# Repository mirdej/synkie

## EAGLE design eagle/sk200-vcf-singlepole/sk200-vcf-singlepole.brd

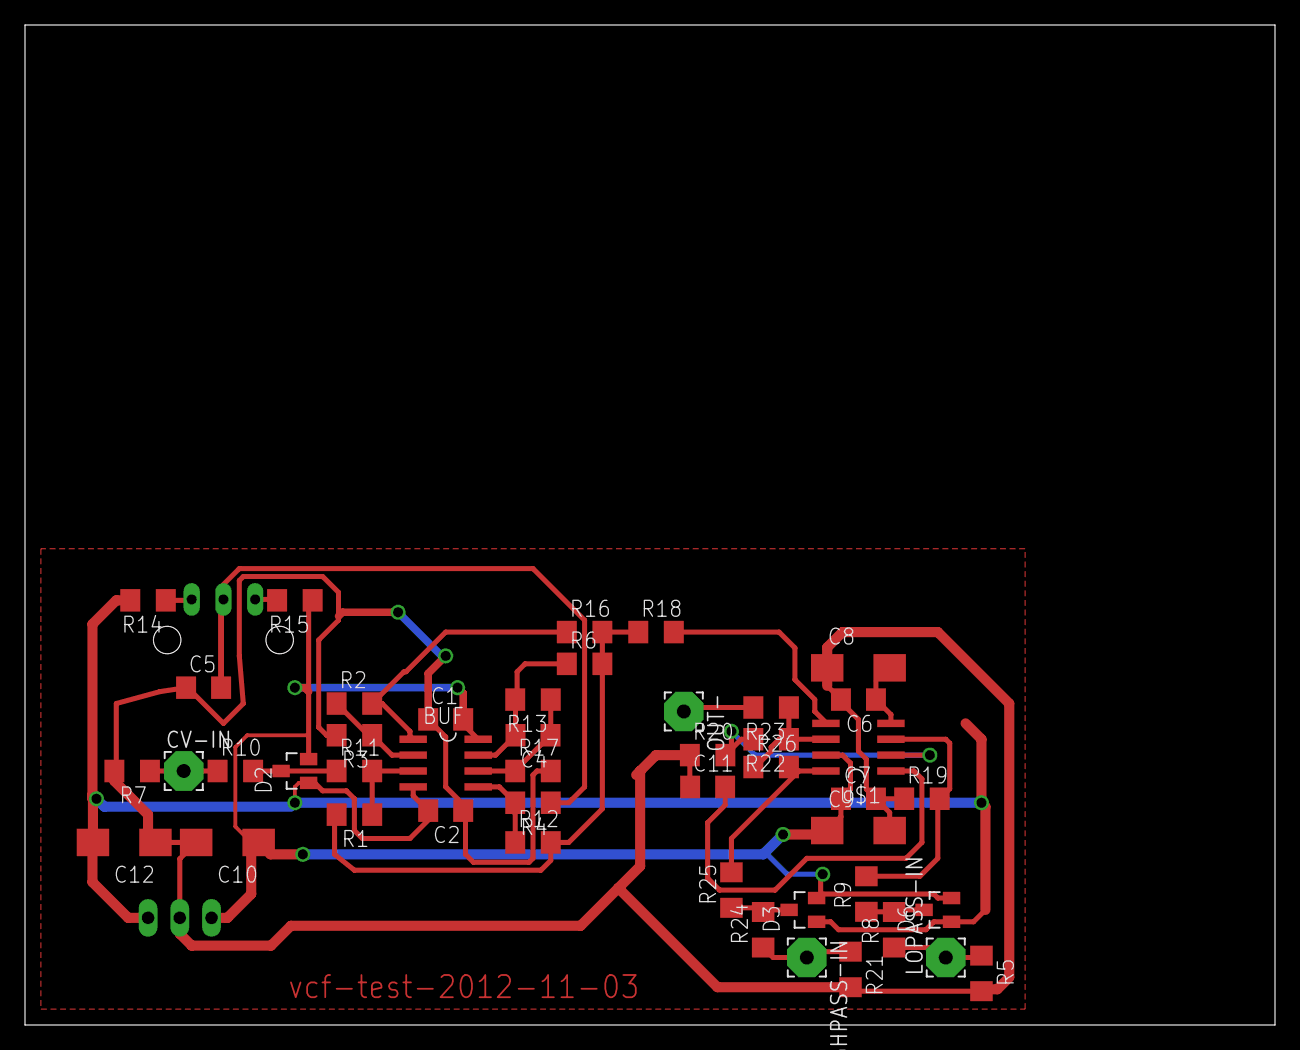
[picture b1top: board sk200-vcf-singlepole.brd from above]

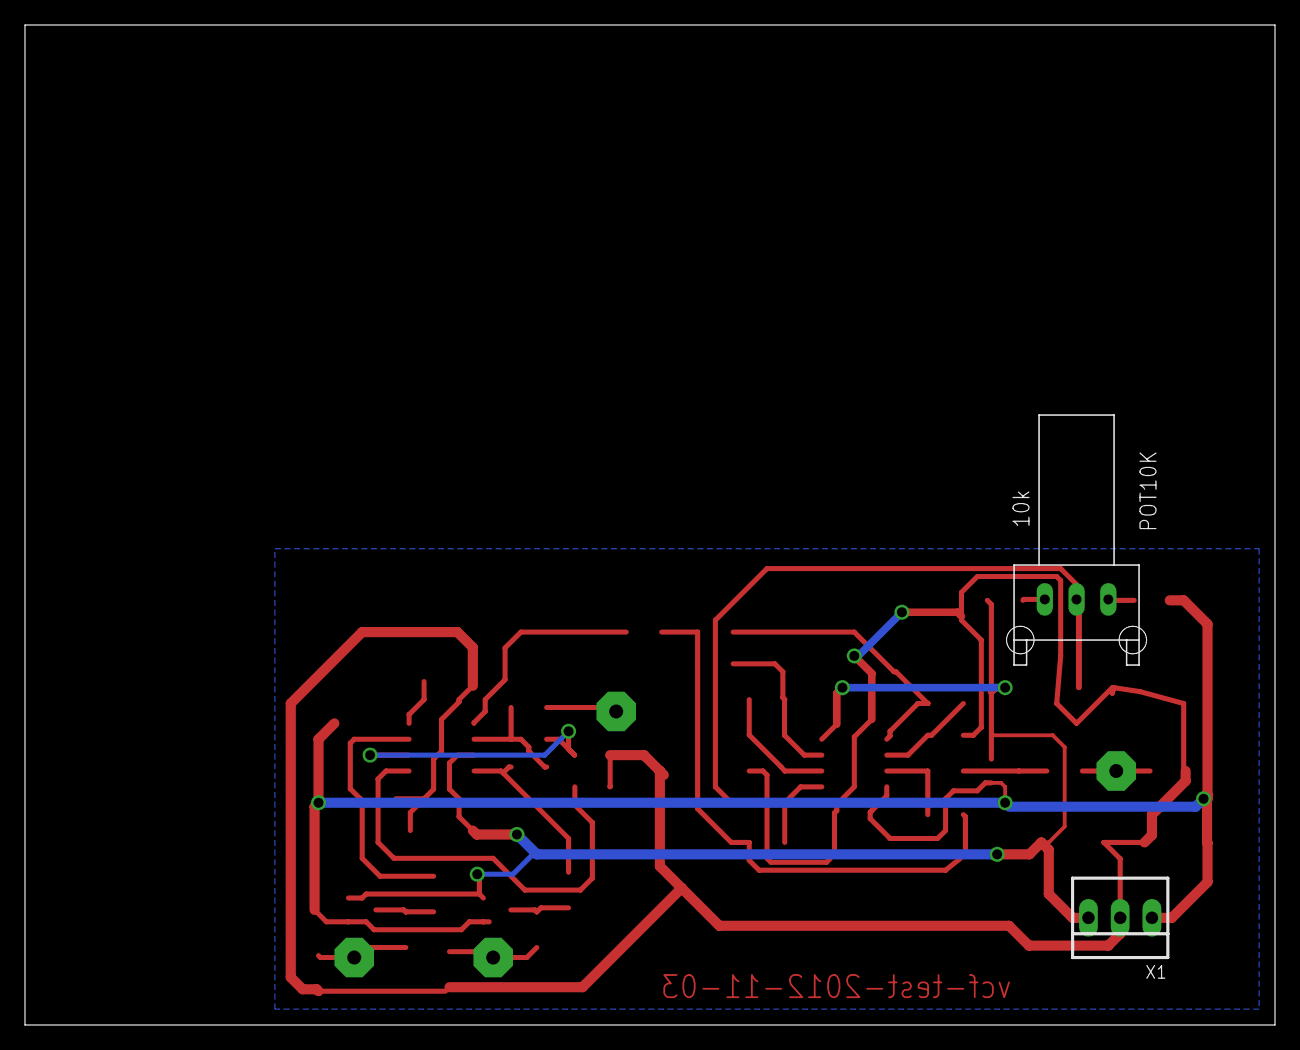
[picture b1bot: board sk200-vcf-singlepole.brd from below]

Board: 2 copper layers, 100.0 x 80.0 mm, 48 parts (2 on the bottom side), 26 nets.

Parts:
BUF: MAX4392ESA; SO08
C1, C2, C5, C6, C7: C1206
C4: 50p; C1206
C8, C9: 2u2tantal; CT6032
C10, C12: CT6032
C11: 330p (470p); C1206
CV-IN: 3,17/1,1
D2, D3, D6: BAT54S-L44; SOT23
HIGHPASS-IN: 3,17/1,1
LOPASS-IN: 3,17/1,1
OUT-: 3,17/1,1
POT10K: 10k; ALPS_RK09K111_H
R1, R2, R3, R11: 100k; R1206
R4, R12, R13, R17: 1M; R1206
R5, R21: 47k; R1206
R6, R9, R16, R22, R25, R26: 1k; R1206
R7: 4k7; R1206
R8, R10, R24: 100; R1206
R14, R15: 20k; R1206
R18: 1k6; R1206
R19, R20: 120; R1206
R23: 75; R1206
U$1: LT1228; SO08
X1: 22-23-2031

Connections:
+5V: BUF.8, C1.2, C7.1, C9.+, C10.+, D2.2, D3.2, D6.2, R15.1, U$1.7, X1.3
-5V: BUF.4, C2.2, C6.1, C8.-, C12.-, D2.1, D3.1, D6.1, R14.2, U$1.4, X1.1
GND: C1.1, C2.1, C5.1, C6.2, C7.2, C8.+, C9.-, C10.-, C11.1, C12.+, R3.2, R5.2, R7.2, R17.2, R19.1, R20.1, R21.2, X1.2
unnamed: C5.2, POT10K.2, R4.1
unnamed: POT10K.1, R14.1
unnamed: POT10K.3, R15.2
unnamed: BUF.2, R2.1, R3.1
unnamed: R9.2, R19.2, U$1.3
unnamed: C11.2, U$1.1
unnamed: BUF.5, R4.2, R12.1
unnamed: BUF.7, C4.2, R6.1, R13.2
unnamed: R20.2, R22.2, U$1.2
unnamed: CV-IN.1, R7.1, R10.1
unnamed: D2.3, R10.2, R11.1
unnamed: BUF.6, C4.1, R13.1, R17.1
unnamed: BUF.3, R1.1, R11.2
unnamed: LOPASS-IN.1, R5.1, R8.1
unnamed: D6.3, R8.2, R9.1
unnamed: BUF.1, R2.2, R16.1
unnamed: R18.2, U$1.5
unnamed: R1.2, R6.2, R12.2, R16.2, R18.1
unnamed: R22.1, R23.1, R26.1, U$1.6
unnamed: OUT-.1, R23.2
unnamed: HIGHPASS-IN.1, R21.1, R24.1
unnamed: D3.3, R24.2, R25.1
unnamed: R25.2, R26.2, U$1.8

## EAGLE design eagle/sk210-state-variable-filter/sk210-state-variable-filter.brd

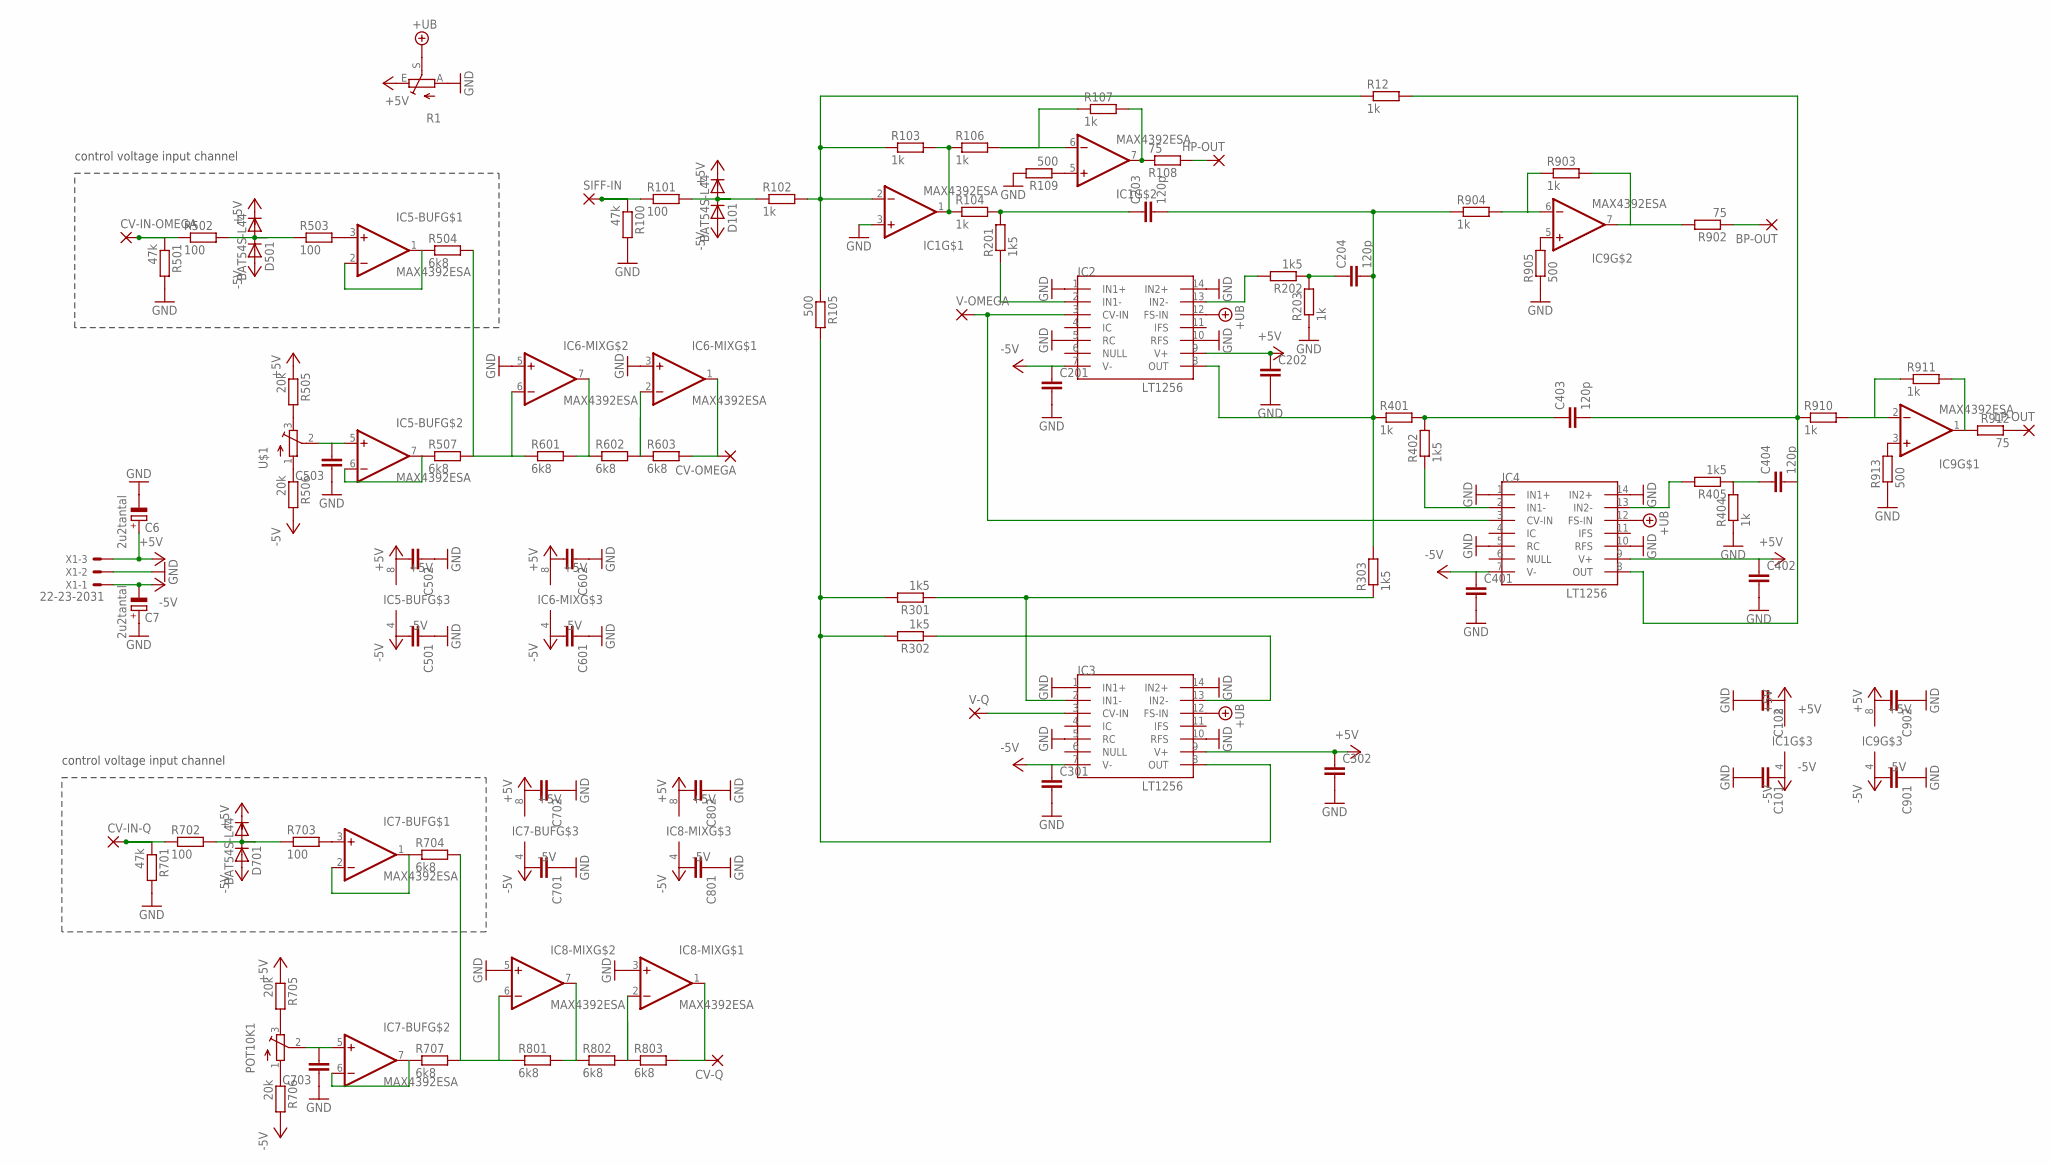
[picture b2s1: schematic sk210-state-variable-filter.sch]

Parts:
BP-OUT: 3,17/1,1
C6, C7: 2u2tantal; CT3528
C101, C102, C201, C202, C301, C302, C401, C402, C501, C502, C503, C601, C602, C701, C702, C703, C801, C802, C901, C902: C-EUC1206; C1206
C203, C204, C403, C404: 120p; C1206
CV-IN-OMEGA: 3,17/1,1
CV-IN-Q: 3,17/1,1
CV-OMEGA: 3,17/1,1
CV-Q: 3,17/1,1
D101, D501, D701: BAT54S-L44; SOT23
HP-OUT: 3,17/1,1
IC1, IC5-BUF, IC6-MIX, IC7-BUF, IC8-MIX, IC9: MAX4392ESA; SO08
IC2, IC3, IC4: LT1256; SO14
LP-OUT: 3,17/1,1
POT10K1: 10k; ALPS_RK09K111
R1: TRIM_EU-B64W; B64W
R12, R102, R103, R104, R106, R107, R203, R401, R404, R903, R904, R910, R911: 1k; R1206
R100, R501, R701: 47k; R1206
R101, R502, R503, R702, R703: 100; R1206
R105, R109, R905, R913: 500; R1206
R108, R902, R912: 75; R1206
R201, R202, R301, R302, R303, R402, R405: 1k5; R1206
R504, R507, R601, R602, R603, R704, R707, R801, R802, R803: 6k8; R1206
R505, R506, R705, R706: 20k; R1206
SIFF-IN: 3,17/1,1
U$1: ALPS_RK09K111_HOHNE-FüSSE; ALPS_RK09K111
V-OMEGA: 3,17/1,1
V-Q: 3,17/1,1
X1: 22-23-2031

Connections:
+5V: C6.+, C102.1, C202.1, C302.1, C402.1, C502.2, C602.2, C702.2, C802.2, C902.2, D101.2 (C), D501.2 (C), D701.2 (C), IC1.8 (+5V), IC2.9 (V+), IC3.9 (V+), IC4.9 (V+), IC5-BUF.8 (+5V), IC6-MIX.8 (+5V), IC7-BUF.8 (+5V), IC8-MIX.8 (+5V), IC9.8 (+5V), R1.E, R505.1, R705.1, X1.3
+UB: IC2.12 (FS-IN), IC3.12 (FS-IN), IC4.12 (FS-IN), R1.S
-5V: C7.-, C101.1, C201.1, C301.1, C401.1, C501.2, C601.2, C701.2, C801.2, C901.2, D101.1 (A), D501.1 (A), D701.1 (A), IC1.4 (-5V), IC2.7 (V-), IC3.7 (V-), IC4.7 (V-), IC5-BUF.4 (-5V), IC6-MIX.4 (-5V), IC7-BUF.4 (-5V), IC8-MIX.4 (-5V), IC9.4 (-5V), R506.2, R706.2, X1.1
GND: C6.-, C7.+, C101.2, C102.2, C201.2, C202.2, C301.2, C302.2, C401.2, C402.2, C501.1, C502.1, C503.1, C601.1, C602.1, C701.1, C702.1, C703.1, C801.1, C802.1, C901.1, C902.1, IC1.3 (+IN), IC2.1 (IN1+), IC2.5 (RC), IC2.10 (RFS), IC2.14 (IN2+), IC3.1 (IN1+), IC3.5 (RC), IC3.10 (RFS), IC3.14 (IN2+), IC4.1 (IN1+), IC4.5 (RC), IC4.10 (RFS), IC4.14 (IN2+), IC6-MIX.3 (+IN), IC6-MIX.5 (+IN), IC8-MIX.3 (+IN), IC8-MIX.5 (+IN), R1.A, R100.2, R109.2, R203.1, R404.1, R501.2, R701.2, R905.1, R913.1, X1.2
unnamed: C503.2, IC5-BUF.5 (+IN), U$1.2 (W)
unnamed: R506.1, U$1.1 (S)
unnamed: R505.2, U$1.3 (E)
unnamed: IC1.7 (OUT), R107.2, R108.1
unnamed: IC1.2 (-IN), R12.1, R102.2, R103.1, R105.1
unnamed: C203.1, R104.2, R201.2
unnamed: C203.2, C204.2, IC2.8 (OUT), R303.2, R401.1, R904.1
unnamed: IC3.2 (IN1-), R301.1, R303.1
unnamed: IC3.8 (OUT), R105.2, R301.2, R302.2
unnamed: CV-IN-OMEGA.1, R501.1, R502.1
unnamed: D501.3 (AC), R502.2, R503.1
unnamed: IC2.2 (IN1-), R201.1
unnamed: IC5-BUF.6 (-IN), IC5-BUF.7 (OUT), R507.1
unnamed: IC5-BUF.3 (+IN), R503.2
unnamed: R100.1, R101.1, SIFF-IN.1
unnamed: D101.3 (AC), R101.2, R102.1
unnamed: IC5-BUF.1 (OUT), IC5-BUF.2 (-IN), R504.1
unnamed: IC3.13 (IN2-), R302.1
unnamed: IC6-MIX.6 (-IN), R504.2, R507.2, R601.1
unnamed: IC6-MIX.7 (OUT), R601.2, R602.1
unnamed: IC6-MIX.2 (-IN), R602.2, R603.1
unnamed: CV-OMEGA.1, IC6-MIX.1 (OUT), R603.2
unnamed: IC3.3 (CV-IN), V-Q.1
unnamed: IC2.3 (CV-IN), IC4.3 (CV-IN), V-OMEGA.1
unnamed: CV-IN-Q.1, R701.1, R702.1
unnamed: IC2.13 (IN2-), R202.2
unnamed: C204.1, R202.1, R203.2
unnamed: C403.1, R401.2, R402.2
unnamed: C403.2, C404.2, IC4.8 (OUT), R12.2, R910.1
unnamed: IC4.2 (IN1-), R402.1
unnamed: D701.3 (AC), R702.2, R703.1
unnamed: C404.1, R404.2, R405.1
unnamed: IC7-BUF.3 (+IN), R703.2
unnamed: IC7-BUF.1 (OUT), IC7-BUF.2 (-IN), R704.1
unnamed: IC7-BUF.6 (-IN), IC7-BUF.7 (OUT), R707.1
unnamed: IC8-MIX.6 (-IN), R704.2, R707.2, R801.1
unnamed: IC8-MIX.7 (OUT), R801.2, R802.1
unnamed: IC8-MIX.2 (-IN), R802.2, R803.1
unnamed: CV-Q.1, IC8-MIX.1 (OUT), R803.2
unnamed: C703.2, IC7-BUF.5 (+IN), POT10K1.2 (W)
unnamed: POT10K1.1 (S), R706.1
unnamed: POT10K1.3 (E), R705.2
unnamed: IC9.1 (OUT), R911.2, R912.2
unnamed: HP-OUT.1, R108.2
unnamed: IC9.7 (OUT), R902.2, R903.2
unnamed: IC1.1 (OUT), R103.2, R104.1, R106.1
unnamed: LP-OUT.1, R912.1
unnamed: BP-OUT.1, R902.1
unnamed: IC9.6 (-IN), R903.1, R904.2
unnamed: IC9.5 (+IN), R905.2
unnamed: IC1.6 (-IN), R106.2, R107.1
unnamed: IC1.5 (+IN), R109.1
unnamed: IC9.2 (-IN), R910.2, R911.1
unnamed: IC9.3 (+IN), R913.2
R403: IC4.13 (IN2-), R405.2

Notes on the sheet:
control voltage input channel

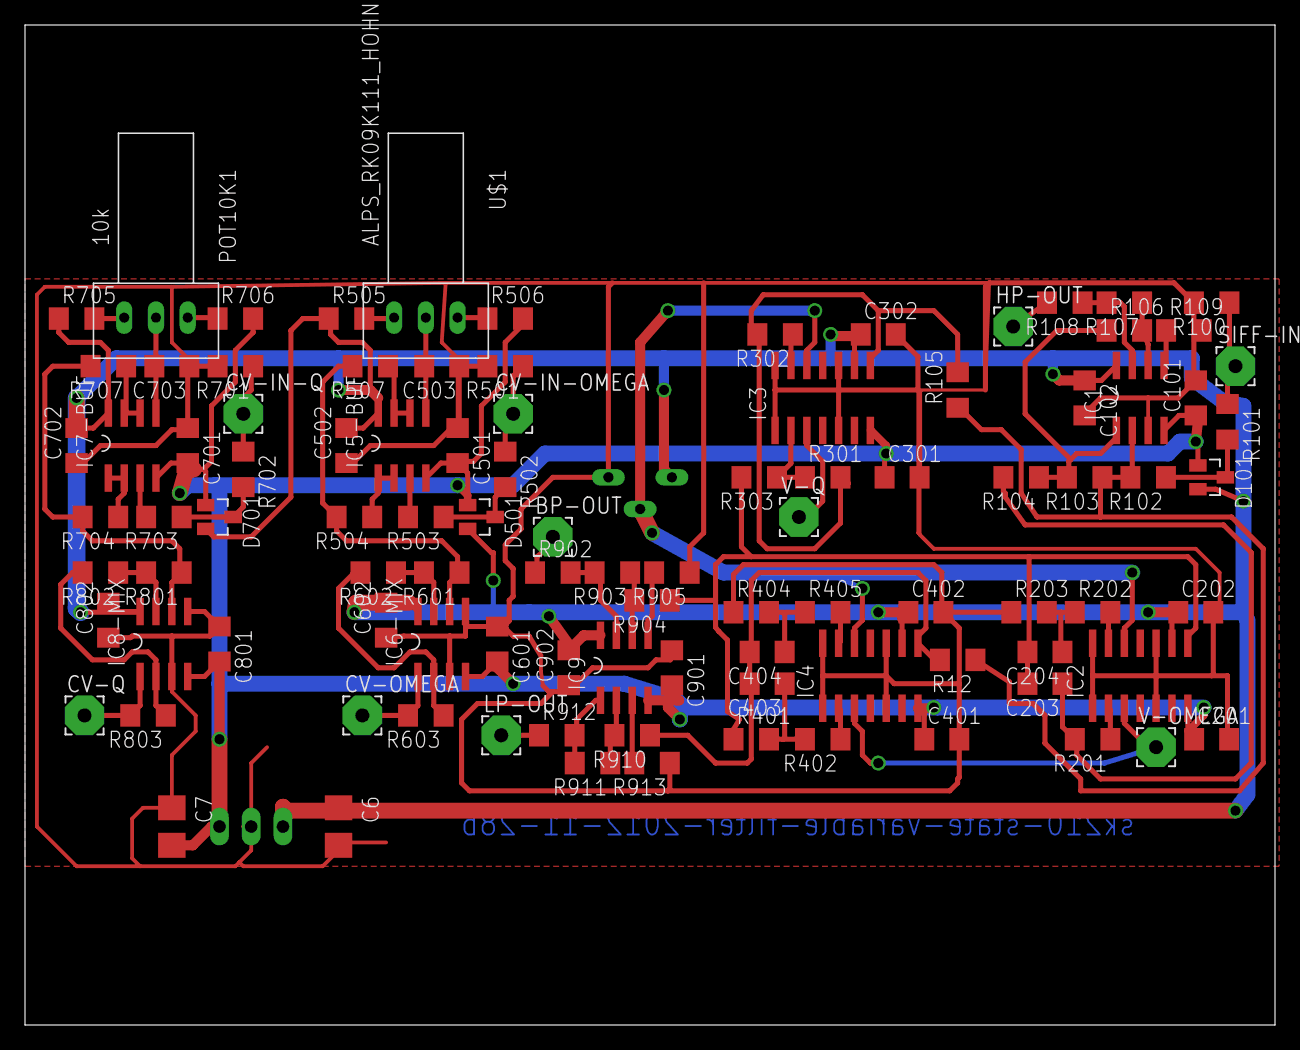
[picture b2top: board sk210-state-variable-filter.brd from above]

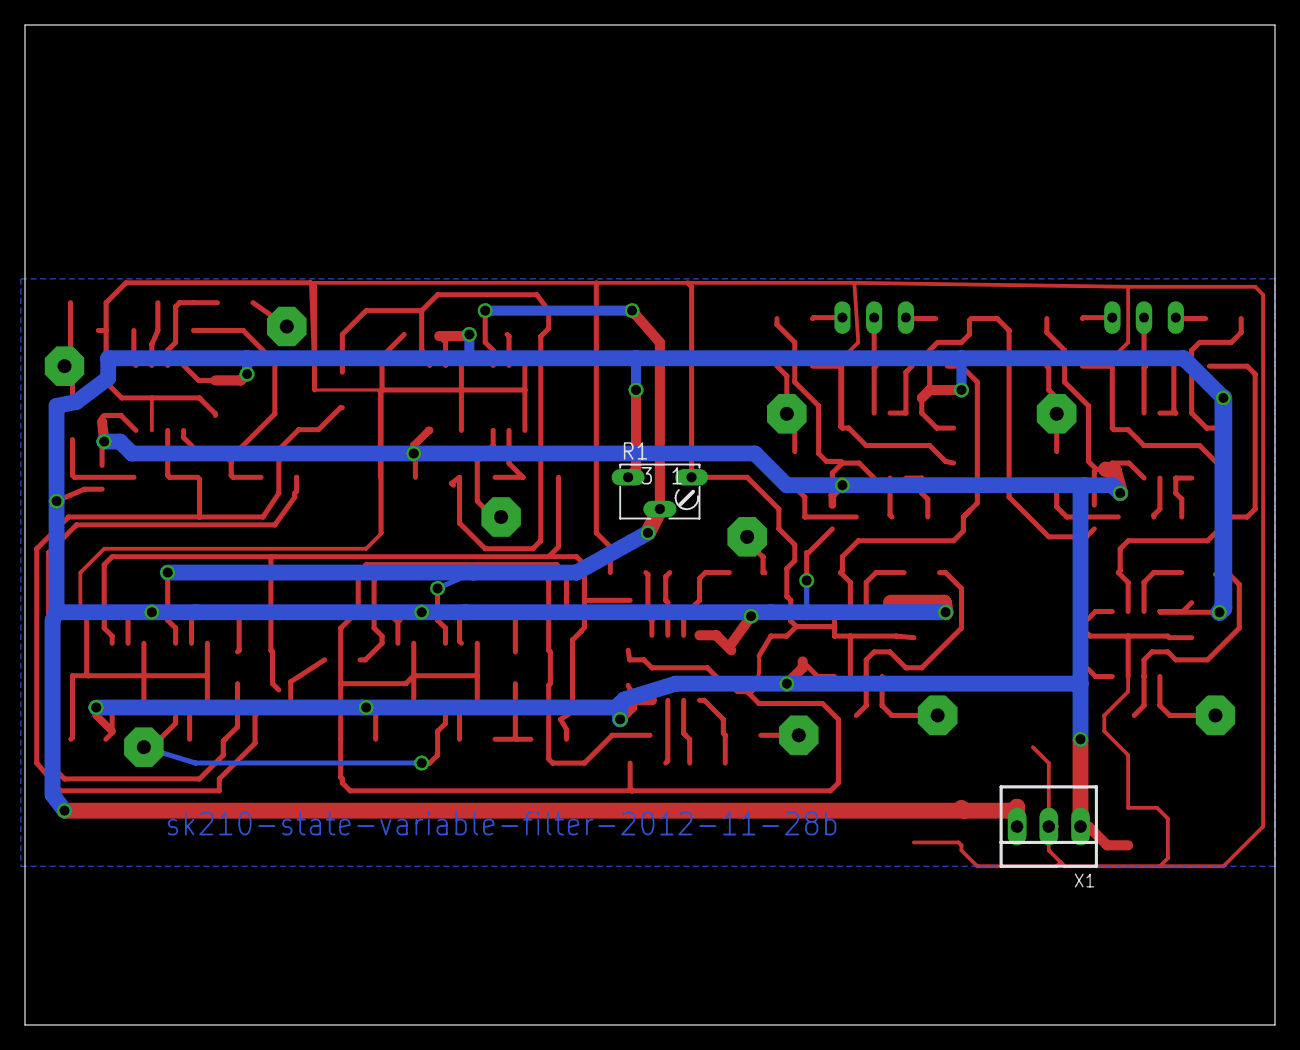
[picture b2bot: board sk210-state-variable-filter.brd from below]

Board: 2 copper layers, 100.0 x 80.0 mm, 101 parts (2 on the bottom side), 59 nets.

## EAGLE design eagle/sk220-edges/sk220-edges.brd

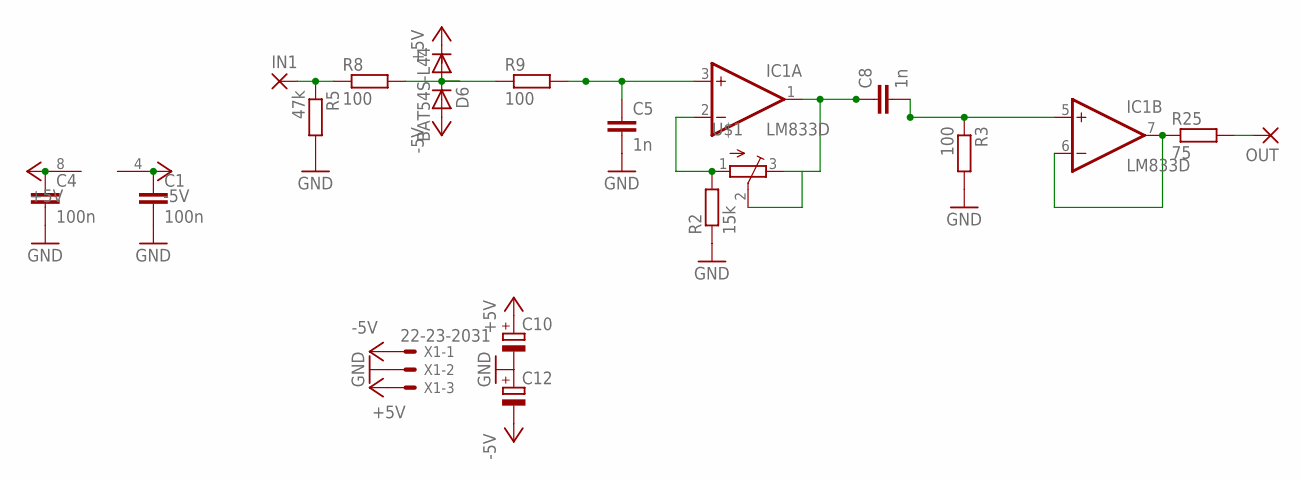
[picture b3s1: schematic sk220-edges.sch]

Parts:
C1, C4: 100n; C0603
C5, C8: 1n; C1206
C10, C12: CPOL-EUSMCB; SMC_B
D6: BAT54S-L44; SOT23
IC1: LM833D; SO08
IN1: 3,81/1,1
OUT: 3,81/1,1
R2: 15k; R1206
R3, R8, R9: 100; R1206
R5: 47k; R1206
R25: 75; R1206
U$1: ALPS_RK09K111_HOHNE-FüSSE; ALPS_RK09K111
X1: 22-23-2031

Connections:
+5V: C4.1, C10.+, D6.2 (C), IC1.8 (V+), X1.3
-5V: C1.1, C12.-, D6.1 (A), IC1.4 (V-), X1.1
GND: C1.2, C4.2, C5.2, C10.-, C12.+, R2.1, R3.2, R5.2, X1.2
unnamed: IC1.2 (-IN), R2.2, U$1.1 (S)
unnamed: OUT.1, R25.2
unnamed: C8.2, IC1.5 (+IN), R3.1
unnamed: C5.1, IC1.3 (+IN), R9.2
unnamed: IC1.6 (-IN), IC1.7 (OUT), R25.1
unnamed: C8.1, IC1.1 (OUT), U$1.2 (W), U$1.3 (E)
unnamed: IN1.1, R5.1, R8.1
unnamed: D6.3 (AC), R8.2, R9.1

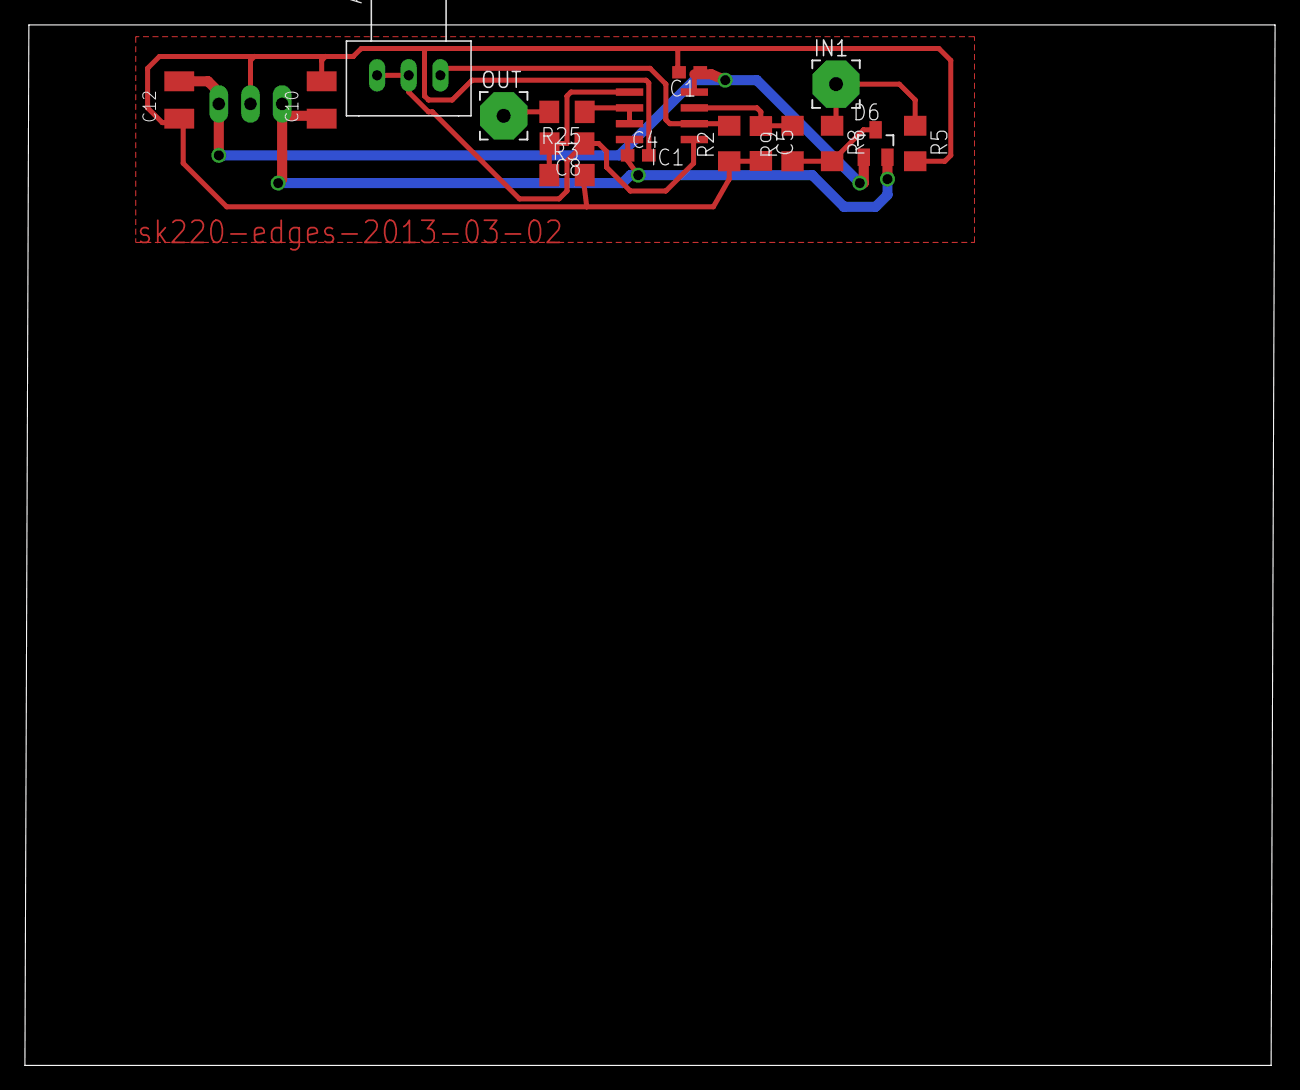
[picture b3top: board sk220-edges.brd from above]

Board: 2 copper layers, 100.3 x 83.5 mm, 18 parts (1 on the bottom side), 11 nets.

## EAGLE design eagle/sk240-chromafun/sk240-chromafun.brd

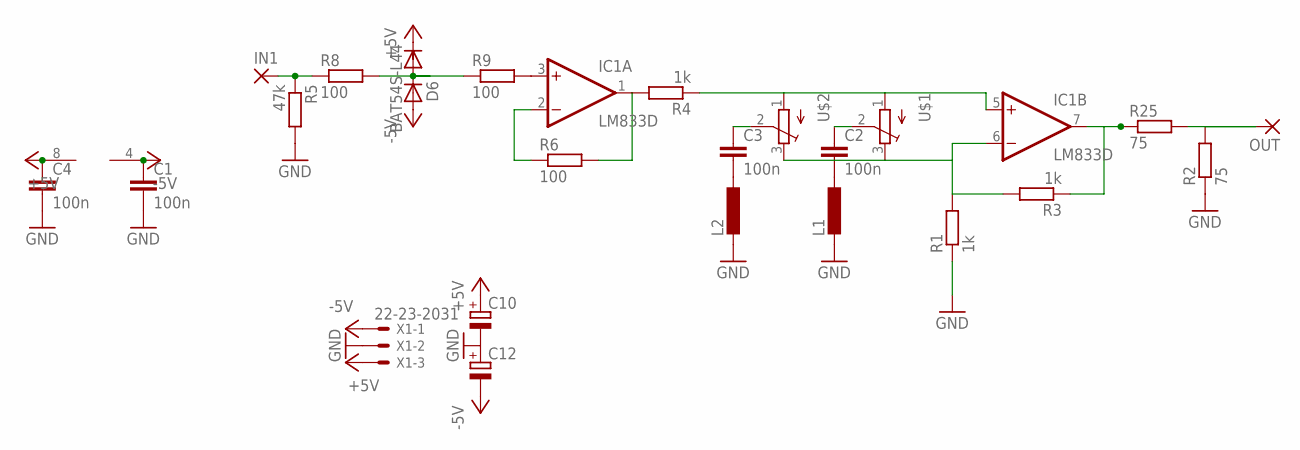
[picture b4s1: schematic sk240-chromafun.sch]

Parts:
C1, C2, C3, C4: 100n; C0603
C10, C12: CPOL-EUSMCB; SMC_B
D6: BAT54S-L44; SOT23
IC1: LM833D; SO08
IN1: 3,81/1,1
L1, L2: L-EU0207/12; 0207/12
OUT: 3,81/1,1
R1, R3, R4: 1k; R1206
R2, R25: 75; R1206
R5: 47k; R1206
R6, R8, R9: 100; R1206
U$1, U$2: ALPS_RK09K111_HOHNE-FüSSE; ALPS_RK09K111
X1: 22-23-2031

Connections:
+5V: C4.1, C10.+, D6.2 (C), IC1.8 (V+), X1.3
-5V: C1.1, C12.-, D6.1 (A), IC1.4 (V-), X1.1
GND: C1.2, C4.2, C10.-, C12.+, L1.2, L2.2, R1.1, R2.1, R5.2, X1.2
unnamed: IC1.1 (OUT), R4.2, R6.2
unnamed: OUT.1, R2.2, R25.2
unnamed: IC1.3 (+IN), R9.2
unnamed: IC1.7 (OUT), R3.1, R25.1
unnamed: IC1.6 (-IN), R1.2, R3.2, U$1.3 (E), U$2.3 (E)
unnamed: IC1.5 (+IN), R4.1, U$1.1 (S), U$2.1 (S)
unnamed: C2.1, U$1.2 (W)
unnamed: C2.2, L1.1
unnamed: C3.1, U$2.2 (W)
unnamed: C3.2, L2.1
unnamed: IC1.2 (-IN), R6.1
unnamed: IN1.1, R5.1, R8.1
unnamed: D6.3 (AC), R8.2, R9.1

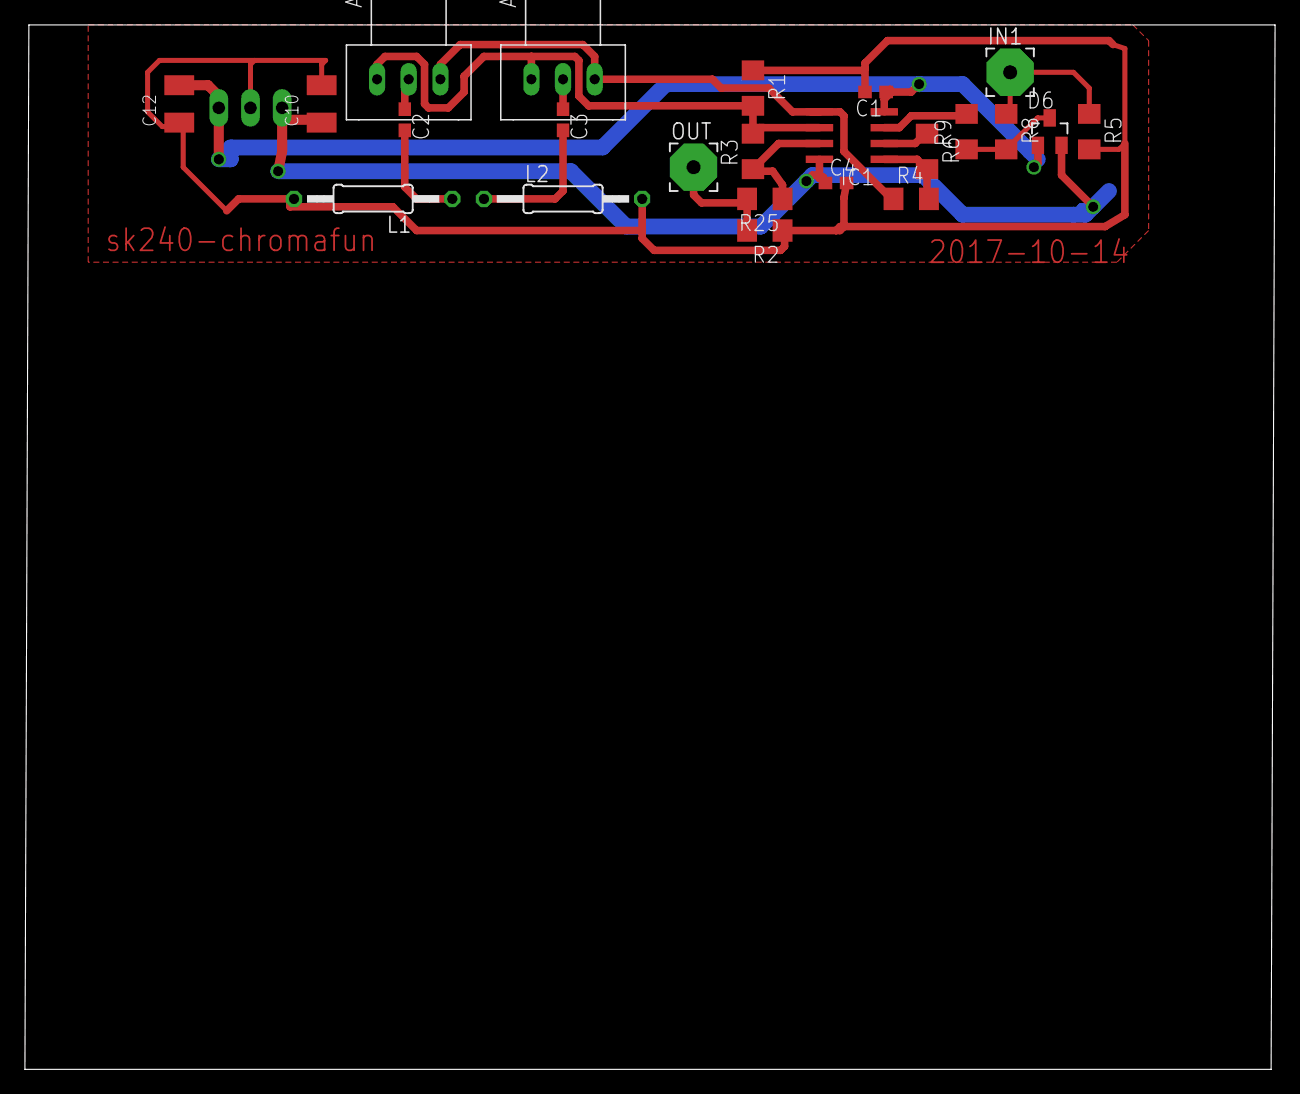
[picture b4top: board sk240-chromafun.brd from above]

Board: 2 copper layers, 100.3 x 83.8 mm, 24 parts (1 on the bottom side), 16 nets.

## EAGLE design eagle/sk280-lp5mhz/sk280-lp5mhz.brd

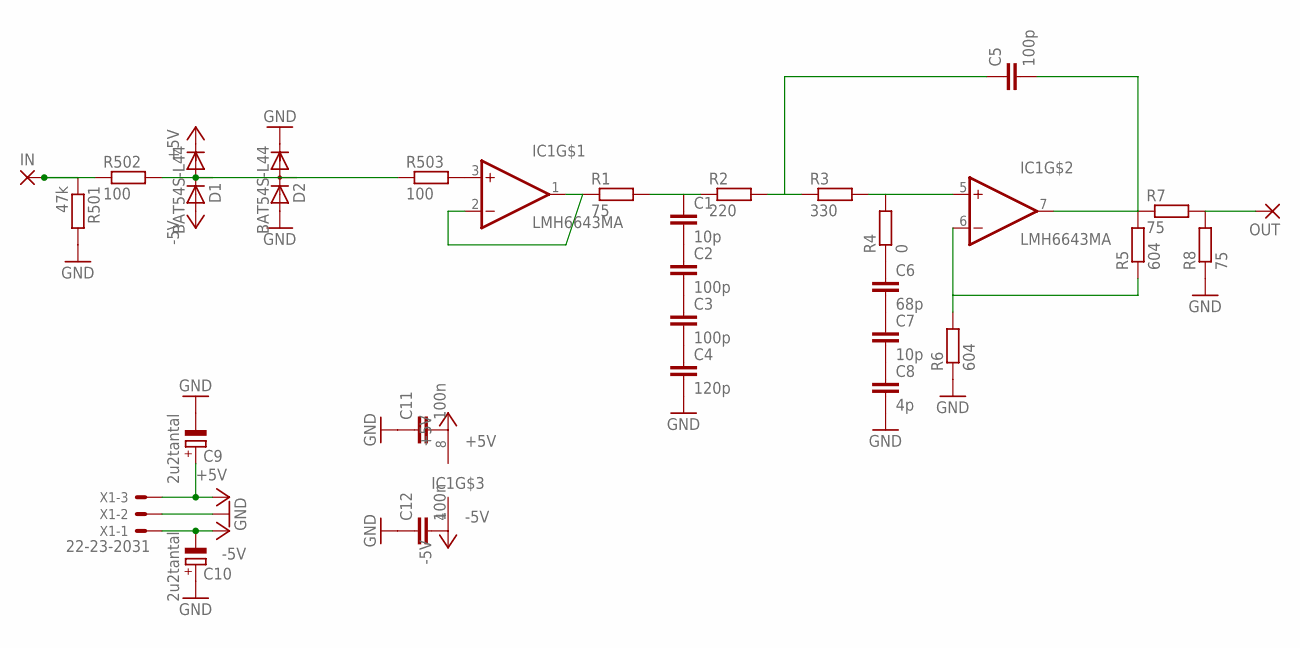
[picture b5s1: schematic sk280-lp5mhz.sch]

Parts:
C1, C7: 10p; C1206
C2, C3, C5: 100p; C1206
C4: 120p; C1206
C6: 68p; C1206
C8: 4p; C1206
C9, C10: 2u2tantal; CT3528
C11, C12: 100n; C0603
D1, D2: BAT54S-L44; SOT23
IC1: LMH6643MA; SO08
IN: 3,17/1,1
OUT: 3,17/1,1
R1, R7, R8: 75; R1206
R2: 220; R1206
R3: 330; R1206
R4: 0; R1206
R5, R6: 604; R1206
R501: 47k; R1206
R502, R503: 100; R1206
X1: 22-23-2031

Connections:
+5V: C9.+, C11.2, D1.2 (C), IC1.8 (+5V), X1.3
-5V: C10.-, C12.2, D1.1 (A), IC1.4 (-5V), X1.1
GND: C4.2, C8.2, C9.-, C10.+, C11.1, C12.1, D2.1 (A), D2.2 (C), R6.1, R8.1, R501.2, X1.2
unnamed: IC1.3 (+IN), R503.2
unnamed: IC1.1 (OUT), IC1.2 (-IN), R1.1
unnamed: C1.2, C2.1
unnamed: C2.2, C3.1
unnamed: C3.2, C4.1
unnamed: C1.1, R1.2, R2.1
unnamed: C5.1, R2.2, R3.1
unnamed: IC1.5 (+IN), R3.2, R4.2
unnamed: C5.2, IC1.7 (OUT), R5.2, R7.1
unnamed: IN.1, R501.1, R502.1
unnamed: D1.3 (AC), D2.3 (AC), R502.2, R503.1
unnamed: C6.1, R4.1
unnamed: C6.2, C7.1
unnamed: C7.2, C8.1
unnamed: IC1.6 (-IN), R5.1, R6.2
unnamed: OUT.1, R7.2, R8.2

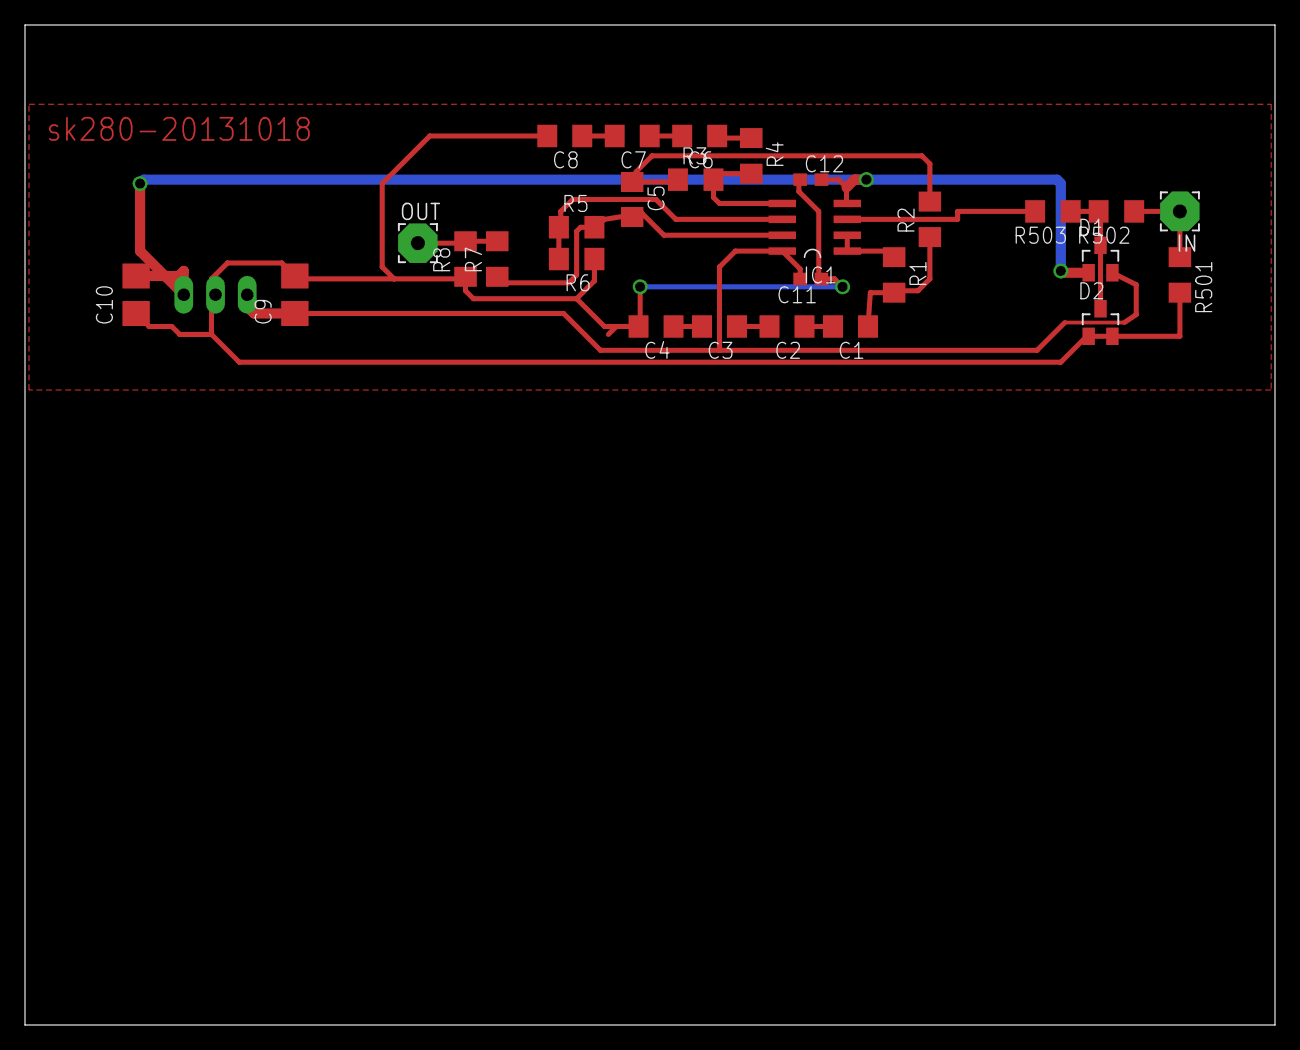
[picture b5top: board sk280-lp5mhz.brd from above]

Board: 2 copper layers, 100.0 x 80.0 mm, 29 parts (1 on the bottom side), 19 nets.

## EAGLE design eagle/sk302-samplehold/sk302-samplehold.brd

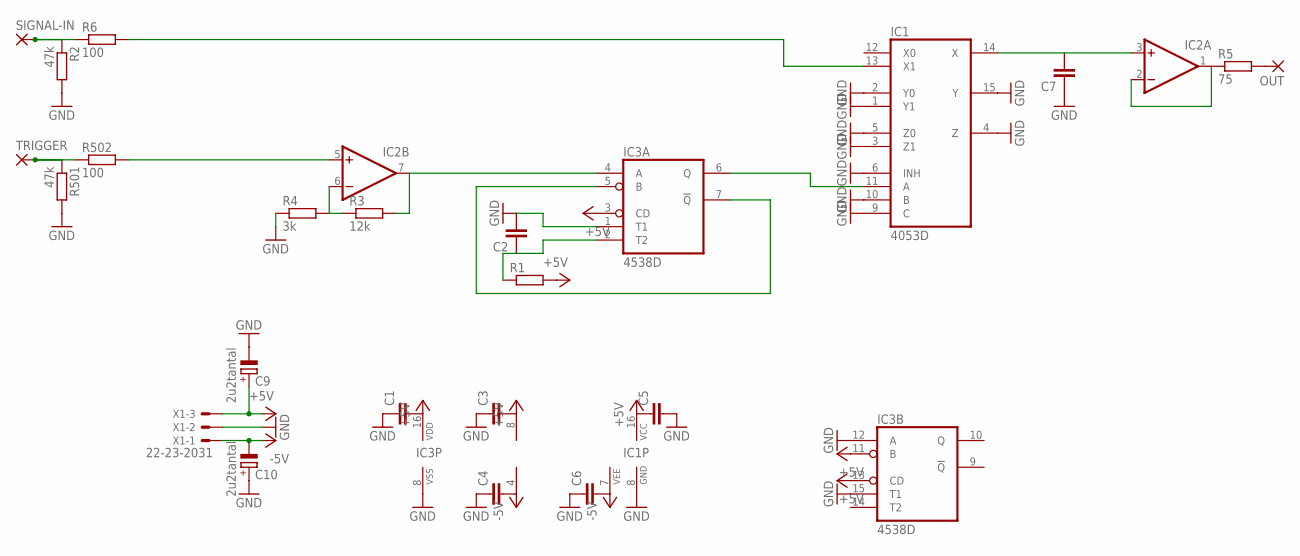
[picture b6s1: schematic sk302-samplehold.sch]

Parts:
C1, C2, C3, C4, C5, C6, C7: C-EUC1206; C1206
C9, C10: 2u2tantal; CT3528
IC1: 4053D; SO16
IC2: DUAL_OPAMPD; SO08
IC3: 4538D; SO16
OUT: 3,17/1,1
R1: R-EU_R1206; R1206
R2, R501: 47k; R1206
R3: 12k; R1206
R4: 3k; R1206
R5: 75; R1206
R6, R502: 100; R1206
SIGNAL-IN: 3,17/1,1
TRIGGER: 3,17/1,1
X1: 22-23-2031

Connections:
+5V: C1.2, C3.2, C5.1, C9.+, IC1.16 (VCC), IC2.8 (V+), IC3.3 (CD), IC3.11 (B), IC3.13 (CD), IC3.16 (VDD), R1.2, X1.3
-5V: C4.2, C6.2, C10.-, IC1.7 (VEE), IC2.4 (V-), X1.1
GND: C1.1, C2.2, C3.1, C4.1, C5.2, C6.1, C7.1, C9.-, C10.+, IC1.1 (Y1), IC1.2 (Y0), IC1.3 (Z1), IC1.4 (Z), IC1.5 (Z0), IC1.6 (INH), IC1.8 (GND), IC1.9 (C), IC1.10 (B), IC1.15 (Y), IC3.1 (T1), IC3.8 (VSS), IC3.12 (A), IC3.15 (T1), R2.2, R4.1, R501.2, X1.2
unnamed: IC2.7 (OUT), IC3.4 (A), R3.2
unnamed: OUT.1, R5.2
unnamed: C2.1, IC3.2 (T2), R1.1
unnamed: R2.1, R6.1, SIGNAL-IN.1
unnamed: IC1.13 (X1), R6.2
unnamed: C7.2, IC1.14 (X), IC2.3 (+IN)
unnamed: IC1.11 (A), IC3.6 (Q)
unnamed: R501.1, R502.1, TRIGGER.1
unnamed: IC2.5 (+IN), R502.2
unnamed: IC2.6 (-IN), R3.1, R4.2
unnamed: IC2.1 (OUT), IC2.2 (-IN), R5.1
unnamed: IC3.5 (B), IC3.7 (!Q)

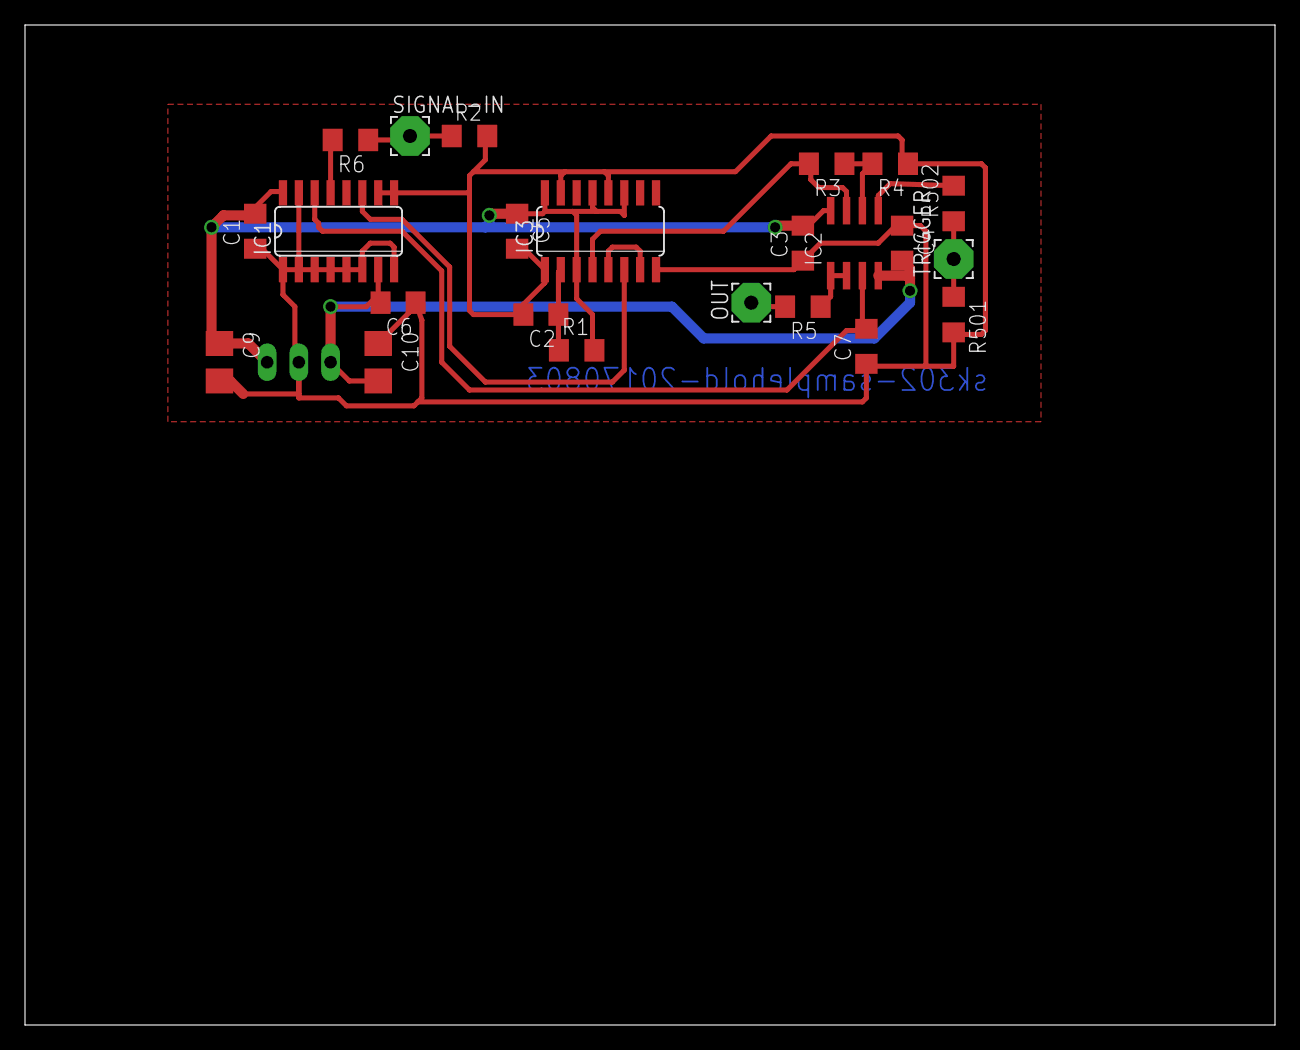
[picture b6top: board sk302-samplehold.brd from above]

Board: 2 copper layers, 100.0 x 80.0 mm, 24 parts (1 on the bottom side), 15 nets.
